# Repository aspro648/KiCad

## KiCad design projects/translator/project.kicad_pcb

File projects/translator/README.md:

ISP Translator
----------------

Intro

Bill Of Materials
----------------
  
- 1 ea., Perfect Purple PCB from OSH Park, with not so perfect layout from [design_files](design_files/) folder.
- 1 ea., U1, IC TRNSLTR BIDIRECTIONAL 14SOIC, TI TXB0104D, https://www.digikey.com/short/j5d3ph
- 1 ea., U2, IC REG LINEAR 3.3V 150MA SOT23-5, MIC5225-3.3YM5-TR, https://www.digikey.com/short/jb2rq8
- 2 ea., C1, C3, 10uF SMD 0805, https://www.digikey.com/short/j5d39w 
- 1 ea., C2 1uF SMD 0603, https://www.digikey.com/short/j5d397
- 1 ea., R1, RES SMD 330 OHM 5% 1/10W 0603, Yageo RC0603JR-07330RL, https://www.digikey.com/short/3wzz20
- 1 ea., R2, 100K ohm 0603 SMD resistor, https://www.digikey.com/short/j5d3b3
- 1 ea., D1, 603 SMD LED amber, https://www.digikey.com/short/j5h3h5
- 2 ea., CON1, CON2, CONN HEADER 6POS .100 STR TIN, http://www.digikey.com/short/3m33n0
- 2 ea., CONN SOCKET IDC 6POS DL SR 30AU, https://www.digikey.com/short/71rdpt
- ribbon cable

Design Files
----------------
This project is designed using Open Source [KiCad](http://kicad-pcb.org/). Design files are located in the [design_files](design_files/) folder.  You can oogle the [schematic](docs/project.sch.pdf).

Firmware
----------------
TBD

Assembly Instructions
----------------
TBD

License
----------------
[Attribution-ShareAlike 3.0 United States (CC BY-SA 3.0 US)](https://creativecommons.org/licenses/by-sa/3.0/us/)

You are free to:

- Share — copy and redistribute the material in any medium or format
- Adapt — remix, transform, and build upon the material

Under the following terms:

- Attribution — You must give appropriate credit, provide a link to the license, and indicate if changes were made. You may do so in any reasonable manner, but not in any way that suggests the licensor endorses you or your use.
- ShareAlike — If you remix, transform, or build upon the material, you must distribute your contributions under the same license as the original.

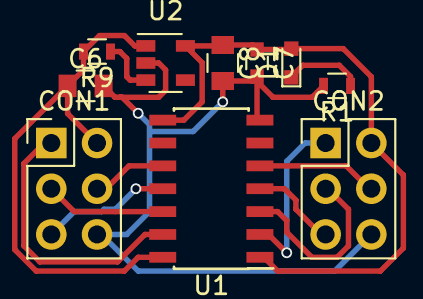
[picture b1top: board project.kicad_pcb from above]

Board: 2 copper layers, 10 parts (0 on the bottom side), 13 nets.

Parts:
C6, C8: 10uF; C_0805
C7: 1uF; C_0603
CON1, CON2: AVR-ISP-6; Pin_Header_Straight_2x03_Pitch2.54mm
D1: LED; LED_0603
R1: 330; R_0603
R9: 100K; R_0603
U1: TXB0104D; SOIC-14_3.9x8.7mm_Pitch1.27mm
U2: MIC5225-3.3; SOT-23-5

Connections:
+3V3: C7.1, C8.1, CON2.2, D1.2, U1.1, U1.8, U2.5
+5V: C6.1, CON1.2, R9.2, U1.14, U2.1
/MISO_3V: CON2.1, U1.2
/MISO_5V: CON1.1, U1.13
/MOSI_3V: CON2.4, U1.5
/MOSI_5V: CON1.4, U1.10
/SCK_3V: CON2.3, U1.3
/SCK_5V: CON1.3, U1.12
/~RESET_3V: CON2.5, U1.4
/~RESET_5V: CON1.5, U1.11
GND: C6.2, C7.2, C8.2, CON1.6, CON2.6, R1.2, U1.7, U2.2
unnamed: D1.1, R1.1
unnamed: R9.1, U2.3
